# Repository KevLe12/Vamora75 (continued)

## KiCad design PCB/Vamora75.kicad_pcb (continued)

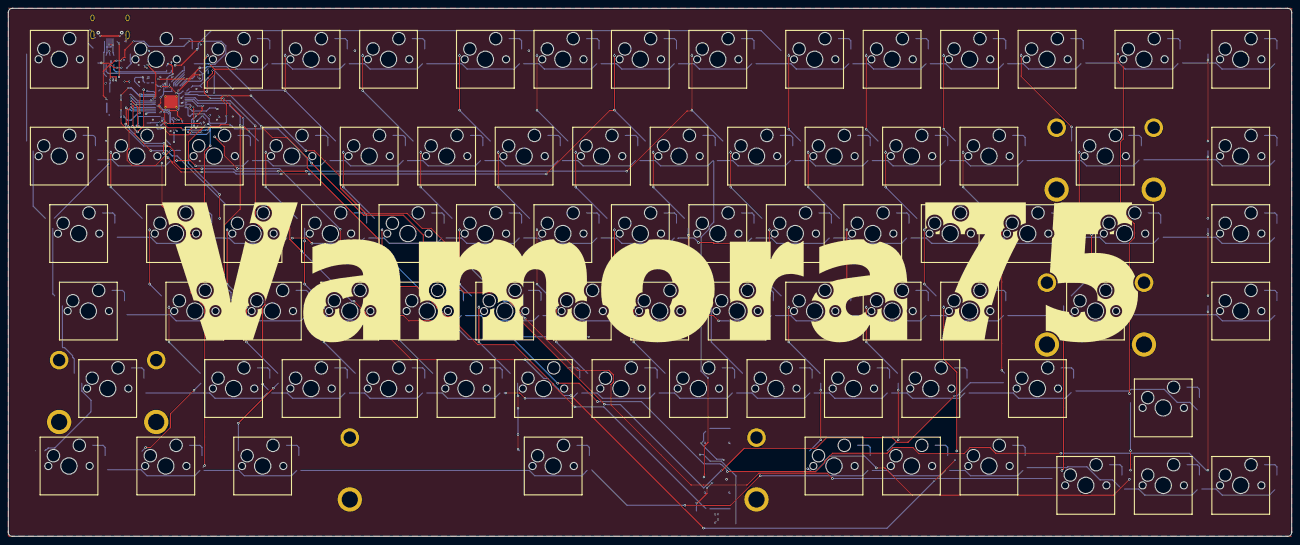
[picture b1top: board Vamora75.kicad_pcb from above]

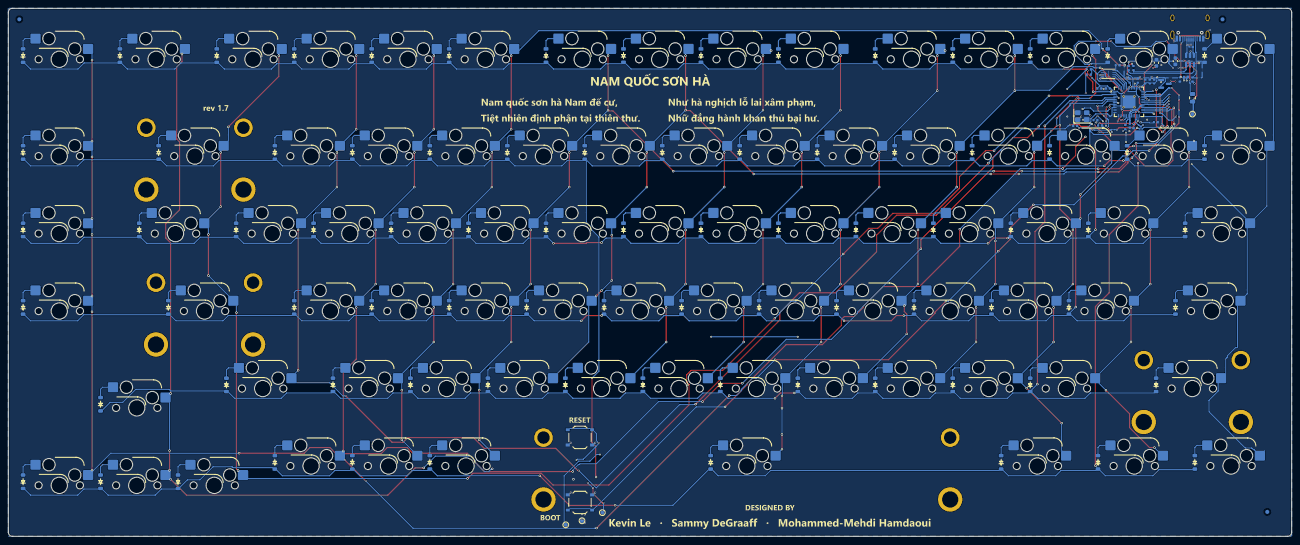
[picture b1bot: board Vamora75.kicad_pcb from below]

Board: 4 copper layers, 315.6 x 129.8 mm, 209 parts (123 on the bottom side), 128 nets.

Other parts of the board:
FID1, FID2, FID3: Fiducial; Fiducial_1mm_Mask2mm
ST1: Stabilizer Backspace; Stabilizer_MX_2.00u
ST2: Stabilizer Enter; Stabilizer_MX_2.00u
ST3: Stabilizer LShift; Stabilizer_MX_2.00u
ST4: Stabilizer Space; Stabilizer_MX_6.25u

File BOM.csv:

Section,Item,Qty,Specification,Designators,LCSC part,Source / file
Kit,PCBA (this design),1,"2-layer FR4 1.6 mm, black mask, ENIG, bottom-side SMT assembled",,,Manufacturing/PCB - JLCPCB/PCBWay
Kit,FR4 plate,1,"1.5 mm (1.6 mm fits), black mask, ENIG for the gold name",,,Manufacturing/Plate - any PCB fab
Kit,Case top,1,PETG/ASA print or CNC 6061,,,Mechanical/Case
Kit,Case bottom,1,"PETG/ASA print or CNC 6061 (solid wedge, 6 deg)",,,Mechanical/Case
Kit,MX-compatible switches,82,3-pin or 5-pin,,,user choice
Kit,Keycaps,82,"1u x 71, 1.25u x 3, 1.5u x 2, 1.75u x 2, 2u x 1, 2.25u x 2, 6.25u x 1",,,"any MX set with a 75 % kit (1.75u RShift, 6.25u space)"
Kit,PCB-mount screw-in stabilisers,4,"3 x 2u (Backspace, Enter, LShift) + 1 x 6.25u (Space)",,,Durock/Cherry/TX
Kit,Gaskets,16,20 x 4.5 x 2 mm Poron 4701-50 or 40A silicone,,,Mechanical/Soft DXF
Kit,Case foam,1,3 mm PE / Poron,,,Mechanical/Soft DXF
Kit,Plate foam (optional),1,"3.5 mm Poron / PE, with stabiliser/wire windows",,,Mechanical/Soft DXF
Kit,Screws,8,M3 x 8 ISO 4762 socket head,,,
Kit,Heat-set inserts,8,M3 x 4 x 4.0 mm heat-set insert (printed top case; tap M3 if CNC),,,
Kit,Dowel pins (split print only),5,3 x 12 mm steel dowel (or printed pin),,,only for the 4-piece printed case
Kit,Bumpers,4,10 x 3 mm silicone bumper,,,
Kit,USB-C cable,1,overmould <= 12.3 x 6.5 mm,,,
PCBA (assembled by JLCPCB),10uF CL10A106KP8NNNC,2,C_0603_1608Metric,"C1,C2",C19702,Manufacturing/PCB/Vamora75_BOM_JLCPCB.csv
PCBA (assembled by JLCPCB),100nF CL05B104KO5NNNC,10,Capacitor_0402,"C3,C4,C5,C6,C7,C9,C10,C11,C12,C15",C1525,Manufacturing/PCB/Vamora75_BOM_JLCPCB.csv
PCBA (assembled by JLCPCB),1uF CL05A105KA5NQNC,2,Capacitor_0402,"C13,C14",C52923,Manufacturing/PCB/Vamora75_BOM_JLCPCB.csv
PCBA (assembled by JLCPCB),15pF 0402CG150J500NT,2,Capacitor_0402,"C16,C17",C1548,Manufacturing/PCB/Vamora75_BOM_JLCPCB.csv
PCBA (assembled by JLCPCB),1N4148W,82,Diode_SOD-123,"D1,D2,D3,D4,D5,D6,D7,D8,D9,D10,D11,D12,D13,D14,D15,D16,D17,D18,D19,D20,D21,D22,D23,D24,D25,D26,D27,D28,D29,D30,D31,D32,D33,D34,D35,D36,D37,D38,D39,D40,D41,D42,D43,D44,D45,D46,D47,D48,D49,D50,D51,D52,D53,D54,D55,D56,D57,D58,D59,D60,D61,D62,D63,D64,D65,D66,D67,D68,D69,D70,D71,D72,D73,D74,D75,D76,D77,D78,D79,D80,D81,D82",C81598,Manufacturing/PCB/Vamora75_BOM_JLCPCB.csv
PCBA (assembled by JLCPCB),500mA SMD0805-050,1,Fuse_0805_2012Metric,F1,C66452,Manufacturing/PCB/Vamora75_BOM_JLCPCB.csv
PCBA (assembled by JLCPCB),HRO TYPE-C-31-M-12,1,USB_C_HRO_TYPE-C-31-M-12,J1,C165948,Manufacturing/PCB/Vamora75_BOM_JLCPCB.csv
PCBA (assembled by JLCPCB),5.1k 0402WGF5101TCE,2,Resistor_0402,"R1,R2",C25905,Manufacturing/PCB/Vamora75_BOM_JLCPCB.csv
PCBA (assembled by JLCPCB),27R 0402WGF270JTCE,2,Resistor_0402,"R3,R4",C25100,Manufacturing/PCB/Vamora75_BOM_JLCPCB.csv
PCBA (assembled by JLCPCB),10k 0402WGF1002TCE,2,Resistor_0402,"R5,R7",C25744,Manufacturing/PCB/Vamora75_BOM_JLCPCB.csv
PCBA (assembled by JLCPCB),1k 0402WGF1001TCE,2,Resistor_0402,"R6,R8",C11702,Manufacturing/PCB/Vamora75_BOM_JLCPCB.csv
PCBA (assembled by JLCPCB),Kailh CPG151101S11 MX hot-swap socket,82,Kailh_CPG151101S11,"SW1,SW2,SW3,SW4,SW5,SW6,SW7,SW8,SW9,SW10,SW11,SW12,SW13,SW14,SW15,SW16,SW17,SW18,SW19,SW20,SW21,SW22,SW23,SW24,SW25,SW26,SW27,SW28,SW29,SW30,SW31,SW32,SW33,SW34,SW35,SW36,SW37,SW38,SW39,SW40,SW41,SW42,SW43,SW44,SW45,SW46,SW47,SW48,SW49,SW50,SW51,SW52,SW53,SW54,SW55,SW56,SW57,SW58,SW59,SW60,SW61,SW62,SW63,SW64,SW65,SW66,SW67,SW68,SW69,SW70,SW71,SW72,SW73,SW74,SW75,SW76,SW77,SW78,SW79,SW80,SW81,SW82",C5156480,Manufacturing/PCB/Vamora75_BOM_JLCPCB.csv
PCBA (assembled by JLCPCB),BOOT TS-1187A-B-A-B,1,SW_Push_1P1T_XKB_TS-1187A,SW90,C318884,Manufacturing/PCB/Vamora75_BOM_JLCPCB.csv
PCBA (assembled by JLCPCB),RESET TS-1187A-B-A-B,1,SW_Push_1P1T_XKB_TS-1187A,SW91,C318884,Manufacturing/PCB/Vamora75_BOM_JLCPCB.csv
PCBA (assembled by JLCPCB),RP2040,1,QFN-56-1EP_7x7mm_P0.4mm_EP3.2x3.2mm_ThermalVias,U1,C2040,Manufacturing/PCB/Vamora75_BOM_JLCPCB.csv
PCBA (assembled by JLCPCB),USBLC6-2SC6,1,ESD_SOT-23-6,U2,C7519,Manufacturing/PCB/Vamora75_BOM_JLCPCB.csv
PCBA (assembled by JLCPCB),XC6206P332MR,1,Voltage_SOT-23,U3,C5446,Manufacturing/PCB/Vamora75_BOM_JLCPCB.csv
PCBA (assembled by JLCPCB),W25Q16JVUXIQ,1,Winbond_USON-8-1EP_3x2mm_P0.5mm_EP0.2x1.6mm,U4,C2843335,Manufacturing/PCB/Vamora75_BOM_JLCPCB.csv
PCBA (assembled by JLCPCB),12MHz ABM8-272-T3,1,Crystal_SMD_3225-4Pin_3.2x2.5mm,Y1,C20625731,Manufacturing/PCB/Vamora75_BOM_JLCPCB.csv

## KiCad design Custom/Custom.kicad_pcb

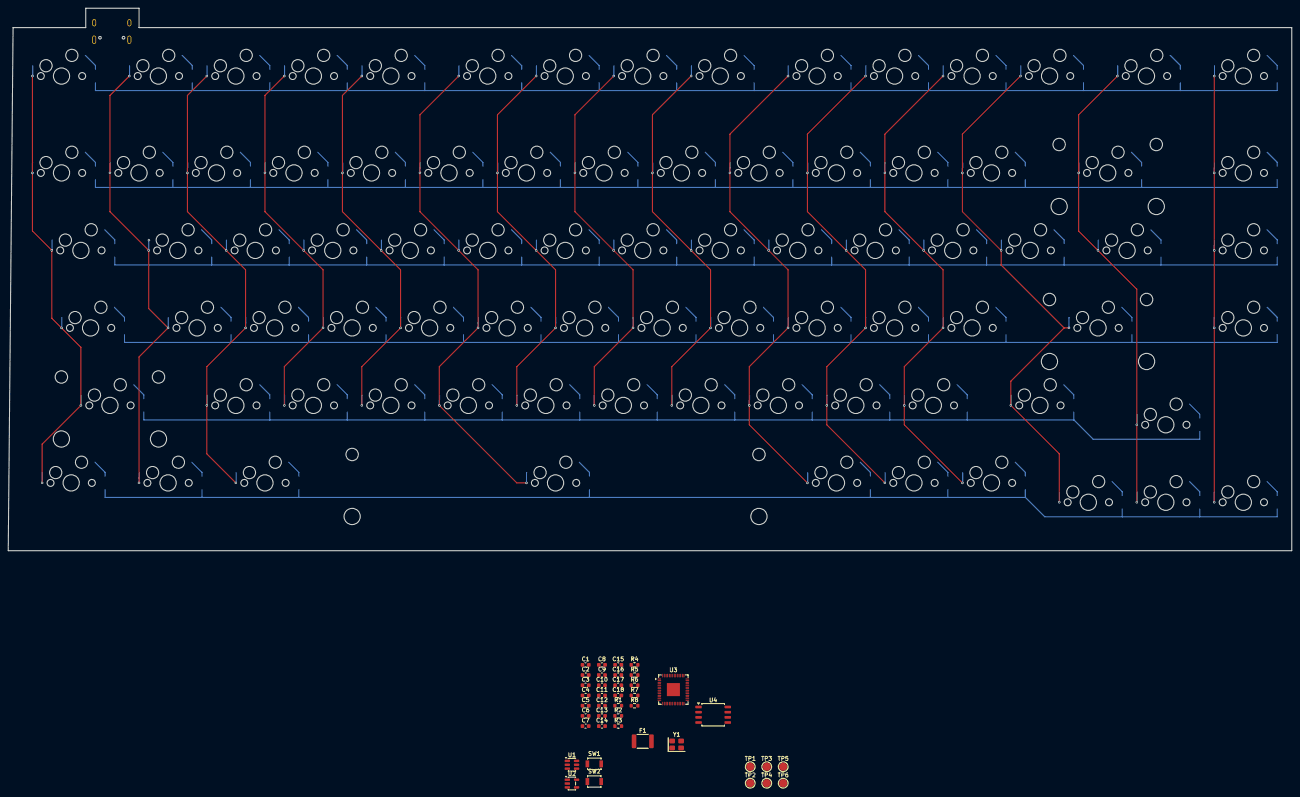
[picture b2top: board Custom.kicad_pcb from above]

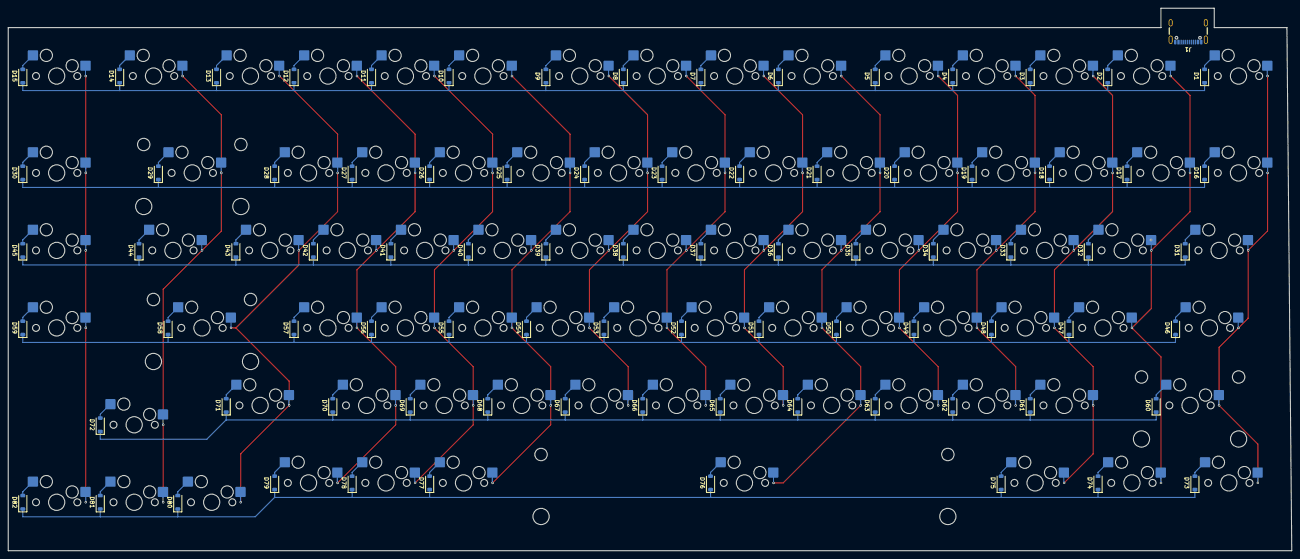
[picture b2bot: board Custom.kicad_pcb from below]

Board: 2 copper layers, 315.5 x 133.4 mm, 205 parts (165 on the bottom side), 129 nets.

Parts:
C1, C7, C8, C9, C10, C11, C12, C13, C14, C15, C17, C18: 100nF; C_0603_1608Metric
C2, C3: 15pF; C_0603_1608Metric
C4, C5, C6, C16: 1uF; C_0603_1608Metric
D1, D2, D3, D4, D5, D6, D7, D8, D9, D10, D11, D12, D13, D14, D15, D16, D17, D18, D19, D20, D21, D22, D23, D24, D25, D26, D27, D28, D29, D30, D31, D32, D33, D34, D35, D36, D37, D38, D39, D40, D41, D42, D43, D44, D45, D46, D47, D48, D49, D50, D51, D52, D53, D54, D55, D56, D57, D58, D59, D60, D61, D62, D63, D64, D65, D66, D67, D68, D69, D70, D71, D72, D73, D74, D75, D76, D77, D78, D79, D80, D81, D82: 1N4148W; D_SOD-123
F1: MF-MSMF050-2; Fuse_1812_4532Metric
J1: USB_C_Receptacle_USB2.0_16P; USB_C_Receptacle_GCT_USB4105-xx-A_16P_TopMnt_Horizontal
R1, R7: 10k; R_0603_1608Metric
R2, R8: 1k; R_0603_1608Metric
R3, R4: 5.1k; R_0603_1608Metric
R5, R6: 27; R_0603_1608Metric
SW1: RESET; SW_SPST_B3U-1000P
SW2: BOOT; SW_SPST_B3U-1000P
SW3, SW4, SW5, SW6, SW7, SW8, SW9, SW10, SW11, SW12, SW13, SW14, SW15, SW16, SW17, SW18, SW19, SW20, SW21, SW22, SW23, SW24, SW25, SW26, SW27, SW28, SW29, SW30, SW32, SW34, SW35, SW36, SW37, SW38, SW39, SW40, SW41, SW42, SW43, SW44, SW45, SW47, SW49, SW50, SW51, SW52, SW53, SW54, SW55, SW56, SW57, SW58, SW59, SW61, SW63, SW64, SW65, SW66, SW67, SW68, SW69, SW70, SW71, SW72, SW74, SW79, SW80, SW81, SW82, SW83, SW84: MX-Hotswap-1U
SW31: MX-Hotswap-2U
SW33, SW46: MX-Hotswap-1.5U
SW48, SW73: MX-Hotswap-1.75U
SW60, SW62: MX-Hotswap-2.25U
SW75, SW76, SW77: MX-Hotswap-1.25U
SW78: MX-Hotswap-6.25U
TP1, TP2, TP3, TP4, TP5, TP6: TestPoint; TestPoint_Pad_D2.0mm
U1: USBLC6-2SC6; SOT-23-6
U2: AP2112K-3.3; SOT-23-5
U3: RP2040; QFN-56-1EP_7x7mm_P0.4mm_EP3.2x3.2mm
U4: W25Q16JVSS; SOIC-8_5.3x5.3mm_P1.27mm
Y1: ABM8-272-T3; Crystal_SMD_3225-4Pin_3.2x2.5mm

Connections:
+1V1: C16.1, C17.1, C18.1, TP2.1 (1_1), U3.23 (DVDD), U3.45 (VREG_VOUT), U3.50 (DVDD)
+3V3: C5.1, C6.1, C7.1, C8.1, C9.1, C10.1, C11.1, C12.1, C13.1, C14.1, C15.1, R1.1, R7.1, TP3.1 (1_1), U2.5 (VOUT), U3.1 (IOVDD), U3.10 (IOVDD), U3.22 (IOVDD), U3.33 (IOVDD), U3.42 (IOVDD), U3.43 (ADC_AVDD), U3.44 (VREG_VIN), U3.48 (USB_VDD), U3.49 (IOVDD), U4.8 (VCC)
+5V: C4.1, F1.2, TP4.1 (1_1), U2.1 (VIN), U2.3 (EN)
/BOOTSEL: R2.2, SW2.1
/CC1: J1.A5 (CC1), R3.1
/CC2: J1.B5 (CC2), R4.1
/QSPI_SCLK: U3.52 (QSPI_SCLK), U4.6 (CLK)
/QSPI_SD0: U3.53 (QSPI_SD0), U4.5 (DI/IO_{0})
/QSPI_SD1: U3.55 (QSPI_SD1), U4.2 (DO/IO_{1})
/QSPI_SD2: U3.54 (QSPI_SD2), U4.3 (~WP/IO_{2})
/QSPI_SD3: U3.51 (QSPI_SD3), U4.7 (~HOLD/~RESET/IO_{3})
/QSPI_SS: R2.1, R7.2, U3.56 (~QSPI_SS), U4.1 (~CS)
/RP_USB_DM: R6.2, U3.46 (USB_DM)
/RP_USB_DP: R5.2, U3.47 (USB_DP)
/RP_XIN: C2.1, U3.20 (XIN), Y1.1
/RP_XOUT: R8.2, U3.21 (XOUT)
/RUN: R1.2, SW1.1, U3.26 (RUN)
/SWCLK_TEST: TP5.1 (1_1), U3.24 (SWCLK)
/SWDIO_TEST: TP6.1 (1_1), U3.25 (SWDIO)
/USB_DM_CONN: J1.A7 (D-), J1.B7 (D-), U1.3 (I/O2)
/USB_DM_PROT: R6.1, U1.4 (I/O2)
/USB_DP_CONN: J1.A6 (D+), J1.B6 (D+), U1.1 (I/O1)
/USB_DP_PROT: R5.1, U1.6 (I/O1)
/VBUS_RAW: C1.1, F1.1, J1.A4 (VBUS), J1.A9 (VBUS), J1.B4 (VBUS), J1.B9 (VBUS), U1.5 (VBUS)
/XTAL_OUT: C3.1, R8.1, Y1.3
COL0: SW3.1, SW18.1, SW33.1, SW48.1, SW62.1, SW75.1, U3.8 (GPIO6)
COL1: SW4.1, SW19.1, SW34.1, SW49.1, SW76.1, U3.9 (GPIO7)
COL2: SW5.1, SW20.1, SW35.1, SW50.1, SW63.1, SW77.1, U3.11 (GPIO8)
COL3: SW6.1, SW21.1, SW36.1, SW51.1, SW64.1, U3.12 (GPIO9)
COL4: SW7.1, SW22.1, SW37.1, SW52.1, SW65.1, U3.13 (GPIO10)
COL5: SW8.1, SW23.1, SW38.1, SW53.1, SW66.1, SW78.1, U3.14 (GPIO11)
COL6: SW9.1, SW24.1, SW39.1, SW54.1, SW67.1, U3.15 (GPIO12)
COL7: SW10.1, SW25.1, SW40.1, SW55.1, SW68.1, U3.16 (GPIO13)
COL8: SW11.1, SW26.1, SW41.1, SW56.1, SW69.1, U3.17 (GPIO14)
COL9: SW12.1, SW27.1, SW42.1, SW57.1, SW70.1, SW79.1, U3.18 (GPIO15)
COL10: SW13.1, SW28.1, SW43.1, SW58.1, SW71.1, SW80.1, U3.27 (GPIO16)
COL11: SW14.1, SW29.1, SW44.1, SW59.1, SW72.1, SW81.1, U3.28 (GPIO17)
COL12: SW15.1, SW30.1, SW45.1, SW60.1, SW73.1, SW82.1, U3.29 (GPIO18)
COL13: SW16.1, SW31.1, SW46.1, SW74.1, SW83.1, U3.30 (GPIO19)
COL14: SW17.1, SW32.1, SW47.1, SW61.1, SW84.1, U3.31 (GPIO20)
GND: C1.2, C2.2, C3.2, C4.2, C5.2, C6.2, C7.2, C8.2, C9.2, C10.2, C11.2, C12.2, C13.2, C14.2, C15.2, C16.2, C17.2, C18.2, J1.A1 (GND), J1.A12 (GND), J1.B1 (GND), J1.B12 (GND), J1.SH (SHIELD), R3.2, R4.2, SW1.2, SW2.2, TP1.1 (1_1), U1.2 (GND), U2.2 (GND), U3.19 (TESTEN), U3.57 (GND), U4.4 (GND), Y1.2 (G), Y1.4 (G)
unnamed: D1.2 (A), SW3.2
unnamed: D2.2 (A), SW4.2
unnamed: D3.2 (A), SW5.2
unnamed: D4.2 (A), SW6.2
unnamed: D5.2 (A), SW7.2
unnamed: D6.2 (A), SW8.2
unnamed: D7.2 (A), SW9.2
unnamed: D8.2 (A), SW10.2
unnamed: D9.2 (A), SW11.2
unnamed: D10.2 (A), SW12.2
unnamed: D11.2 (A), SW13.2
unnamed: D12.2 (A), SW14.2
unnamed: D13.2 (A), SW15.2
unnamed: D14.2 (A), SW16.2
unnamed: D15.2 (A), SW17.2
unnamed: D16.2 (A), SW18.2
unnamed: D17.2 (A), SW19.2
unnamed: D18.2 (A), SW20.2
unnamed: D19.2 (A), SW21.2
unnamed: D20.2 (A), SW22.2
unnamed: D21.2 (A), SW23.2
unnamed: D22.2 (A), SW24.2
unnamed: D23.2 (A), SW25.2
unnamed: D24.2 (A), SW26.2
unnamed: D25.2 (A), SW27.2
unnamed: D26.2 (A), SW28.2
unnamed: D27.2 (A), SW29.2
unnamed: D28.2 (A), SW30.2
unnamed: D29.2 (A), SW31.2
unnamed: D30.2 (A), SW32.2
unnamed: D31.2 (A), SW33.2
unnamed: D32.2 (A), SW34.2
unnamed: D33.2 (A), SW35.2
unnamed: D34.2 (A), SW36.2
unnamed: D35.2 (A), SW37.2
unnamed: D36.2 (A), SW38.2
unnamed: D37.2 (A), SW39.2
unnamed: D38.2 (A), SW40.2
unnamed: D39.2 (A), SW41.2
unnamed: D40.2 (A), SW42.2
unnamed: D41.2 (A), SW43.2
unnamed: D42.2 (A), SW44.2
unnamed: D43.2 (A), SW45.2
unnamed: D44.2 (A), SW46.2
unnamed: D45.2 (A), SW47.2
unnamed: D46.2 (A), SW48.2
unnamed: D47.2 (A), SW49.2
unnamed: D48.2 (A), SW50.2
unnamed: D49.2 (A), SW51.2
unnamed: D50.2 (A), SW52.2
unnamed: D51.2 (A), SW53.2
unnamed: D52.2 (A), SW54.2
unnamed: D53.2 (A), SW55.2
unnamed: D54.2 (A), SW56.2
unnamed: D55.2 (A), SW57.2
unnamed: D56.2 (A), SW58.2
unnamed: D57.2 (A), SW59.2
unnamed: D58.2 (A), SW60.2
unnamed: D59.2 (A), SW61.2
unnamed: D60.2 (A), SW62.2
unnamed: D61.2 (A), SW63.2
unnamed: D62.2 (A), SW64.2
unnamed: D63.2 (A), SW65.2
unnamed: D64.2 (A), SW66.2
unnamed: D65.2 (A), SW67.2
unnamed: D66.2 (A), SW68.2
unnamed: D67.2 (A), SW69.2
unnamed: D68.2 (A), SW70.2
unnamed: D69.2 (A), SW71.2
unnamed: D70.2 (A), SW72.2
unnamed: D71.2 (A), SW73.2
unnamed: D72.2 (A), SW74.2
unnamed: D73.2 (A), SW75.2
unnamed: D74.2 (A), SW76.2
unnamed: D75.2 (A), SW77.2
unnamed: D76.2 (A), SW78.2
unnamed: D77.2 (A), SW79.2
unnamed: D78.2 (A), SW80.2
unnamed: D79.2 (A), SW81.2
unnamed: D80.2 (A), SW82.2
unnamed: D81.2 (A), SW83.2
unnamed: D82.2 (A), SW84.2
ROW0: D1.1 (K), D2.1 (K), D3.1 (K), D4.1 (K), D5.1 (K), D6.1 (K), D7.1 (K), D8.1 (K), D9.1 (K), D10.1 (K), D11.1 (K), D12.1 (K), D13.1 (K), D14.1 (K), D15.1 (K), U3.2 (GPIO0)
ROW1: D16.1 (K), D17.1 (K), D18.1 (K), D19.1 (K), D20.1 (K), D21.1 (K), D22.1 (K), D23.1 (K), D24.1 (K), D25.1 (K), D26.1 (K), D27.1 (K), D28.1 (K), D29.1 (K), D30.1 (K), U3.3 (GPIO1)
ROW2: D31.1 (K), D32.1 (K), D33.1 (K), D34.1 (K), D35.1 (K), D36.1 (K), D37.1 (K), D38.1 (K), D39.1 (K), D40.1 (K), D41.1 (K), D42.1 (K), D43.1 (K), D44.1 (K), D45.1 (K), U3.4 (GPIO2)
ROW3: D46.1 (K), D47.1 (K), D48.1 (K), D49.1 (K), D50.1 (K), D51.1 (K), D52.1 (K), D53.1 (K), D54.1 (K), D55.1 (K), D56.1 (K), D57.1 (K), D58.1 (K), D59.1 (K), U3.5 (GPIO3)
ROW4: D60.1 (K), D61.1 (K), D62.1 (K), D63.1 (K), D64.1 (K), D65.1 (K), D66.1 (K), D67.1 (K), D68.1 (K), D69.1 (K), D70.1 (K), D71.1 (K), D72.1 (K), U3.6 (GPIO4)
ROW5: D73.1 (K), D74.1 (K), D75.1 (K), D76.1 (K), D77.1 (K), D78.1 (K), D79.1 (K), D80.1 (K), D81.1 (K), D82.1 (K), U3.7 (GPIO5)

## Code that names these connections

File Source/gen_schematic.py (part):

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            s.netplan[("U1", num)] = net
    s.pinlabel(u1, "U1", "57", "GND")
    s.pinlabel(u1, "U1", "19", "GND")          # TESTEN
    s.pinlabel(u1, "U1", "26", "RUN")
    s.pinlabel(u1, "U1", "46", "RP_DM")
    s.pinlabel(u1, "U1", "47", "RP_DP")
    for num, net in (("56", "QSPI_SS"), ("52", "QSPI_SCLK"), ("53", "QSPI_SD0"), ("55", "QSPI_SD1"),
                     ("54", "QSPI_SD2"), ("51", "QSPI_SD3")):
        s.pinlabel(u1, "U1", num, net)
    s.pinlabel(u1, "U1", "20", "XIN")
    s.pinlabel(u1, "U1", "21", "XOUT")
    s.nc(u1["24"][:2])          # SWCLK - not needed: ROM USB bootloader + BOOT/RESET buttons
    s.nc(u1["25"][:2])          # SWDIO

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    s.nc(u4["9"][:2])
    r5 = s.place("R", "R5", "10k", g(330), g(240), 0, FP["R0402"], "C25744", "0402WGF1002TCE", "Flash CS pull-up")
    s.pinlabel(r5, "R5", "1", "+3V3")
    s.pinlabel(r5, "R5", "2", "QSPI_SS")
    r6 = s.place("R", "R6", "1k", g(345), g(240), 0, FP["R0402"], "C11702", "0402WGF1001TCE", "BOOTSEL series resistor")
    s.pinlabel(r6, "R6", "1", "QSPI_SS")
    s.pinlabel(r6, "R6", "2", "BOOTSEL")
    sw_boot = s.place("SW_Push", "SW90", "BOOT", g(375), g(255), 0, FP["BTN"], "C318884", "TS-1187A-B-A-B",
                      "Hold while plugging in to enter the RP2040 USB bootloader")
    s.pinlabel(sw_boot, "SW90", "1", "BOOTSEL")
    s.pinlabel(sw_boot, "SW90", "2", "GND")
    r7 = s.place("R", "R7", "10k", g(420), g(240), 0, FP["R0402"], "C25744", "0402WGF1002TCE", "RUN pull-up")
    s.pinlabel(r7, "R7", "1", "+3V3")
    s.pinlabel(r7, "R7", "2", "RUN")
    sw_rst = s.place("SW_Push", "SW91", "RESET", g(450), g(255), 0, FP["BTN"], "C318884", "TS-1187A-B-A-B", "Reset")
    s.pinlabel(sw_rst, "SW91", "1", "RUN")
    s.pinlabel(sw_rst, "SW91", "2", "GND")

    # crystal
    y1 = s.place("Crystal_GND24", "Y1", "12MHz", g(520), g(200), 0, FP["XTAL"], "C20625731", "ABM8-272-T3",
                 "12 MHz, CL 10 pF (Raspberry Pi approved for RP2040)")
    for pin, net in (("1", "XIN"), ("3", "XTAL_OUT"), ("2", "GND"), ("4", "GND")):
        s.netplan[("Y1", pin)] = net
    r8 = s.place("R", "R8", "1k", g(555), g(185), 0, FP["R0402"], "C11702", "0402WGF1001TCE", "XOUT drive limit")
    s.pinlabel(r8, "R8", "1", "XOUT")
    s.netplan[("R8", "2")] = "XTAL_OUT"
    crystal_nodes = {"XIN": [y1["1"][:2]], "XTAL_OUT": [y1["3"][:2], r8["2"][:2]], "GND": [y1["2"][:2]]}
    for i, (ref, net) in enumerate((("C16", "XIN"), ("C17", "XTAL_OUT"))):
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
